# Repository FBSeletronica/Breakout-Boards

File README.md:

# Breakout-Boards
Arduino Breakouts boards for fun

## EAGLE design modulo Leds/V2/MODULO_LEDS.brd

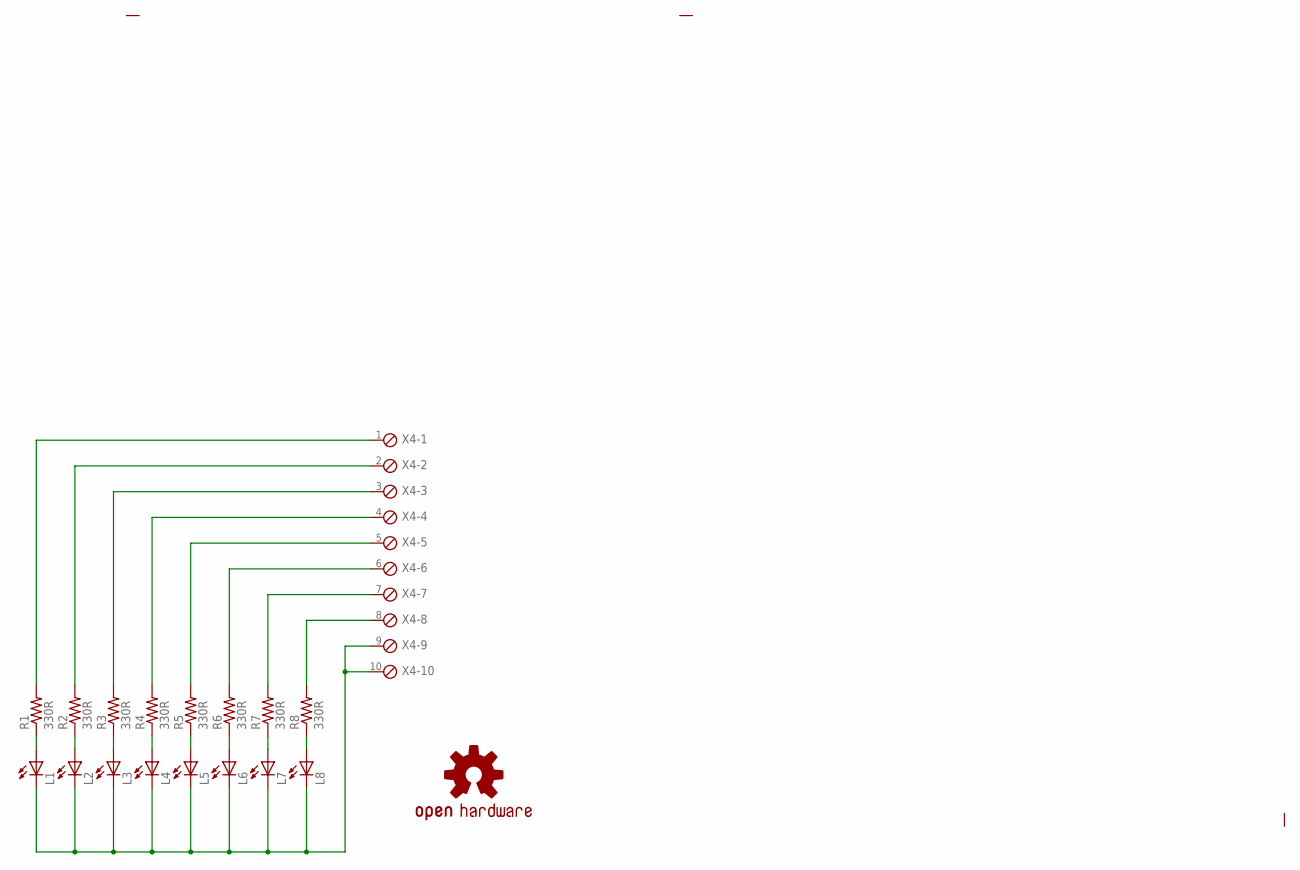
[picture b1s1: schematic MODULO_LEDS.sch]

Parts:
L1, L2, L3, L4, L5, L6, L7, L8: LED3MM
LOGO1: OSHW-LOGOM; OSHW-LOGO-M
R1, R2, R3, R4, R5, R6, R7, R8: 330R; AXIAL-0.4
X4: MPT10; 10POL254

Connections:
unnamed: L1.A, R1.P$1 (1)
unnamed: L2.A, R2.P$1 (1)
unnamed: L3.A, R3.P$1 (1)
unnamed: L4.A, R4.P$1 (1)
unnamed: L1.K (C), L2.K (C), L3.K (C), L4.K (C), L5.K (C), L6.K (C), L7.K (C), L8.K (C), X4.9, X4.10
unnamed: L5.A, R5.P$1 (1)
unnamed: L6.A, R6.P$1 (1)
unnamed: L7.A, R7.P$1 (1)
unnamed: L8.A, R8.P$1 (1)
unnamed: R1.P$2 (2), X4.1
unnamed: R2.P$2 (2), X4.2
unnamed: R3.P$2 (2), X4.3
unnamed: R4.P$2 (2), X4.4
unnamed: R5.P$2 (2), X4.5
unnamed: R6.P$2 (2), X4.6
unnamed: R7.P$2 (2), X4.7
unnamed: R8.P$2 (2), X4.8

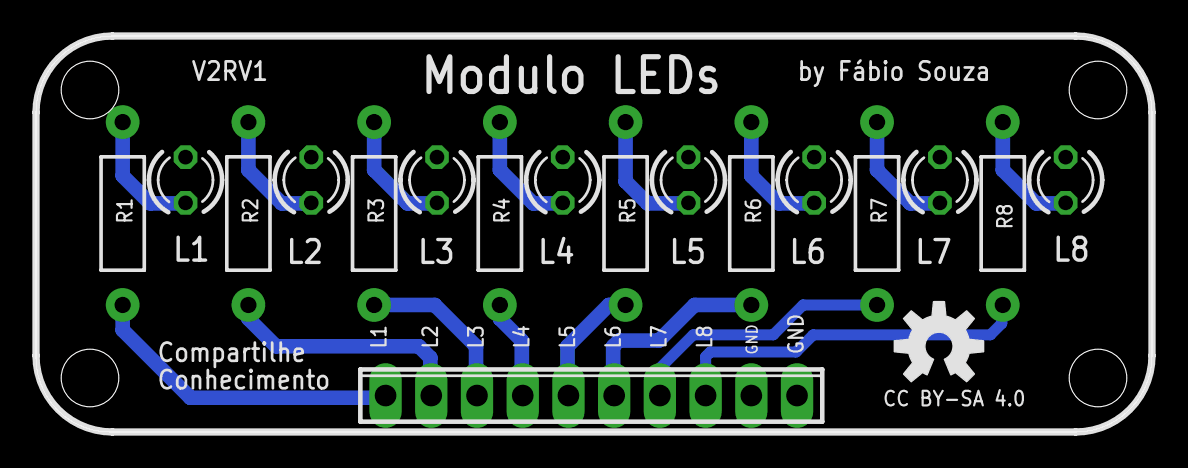
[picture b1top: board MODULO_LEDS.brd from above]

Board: 2 copper layers, 62.0 x 22.0 mm, 18 parts (0 on the bottom side), 17 nets.

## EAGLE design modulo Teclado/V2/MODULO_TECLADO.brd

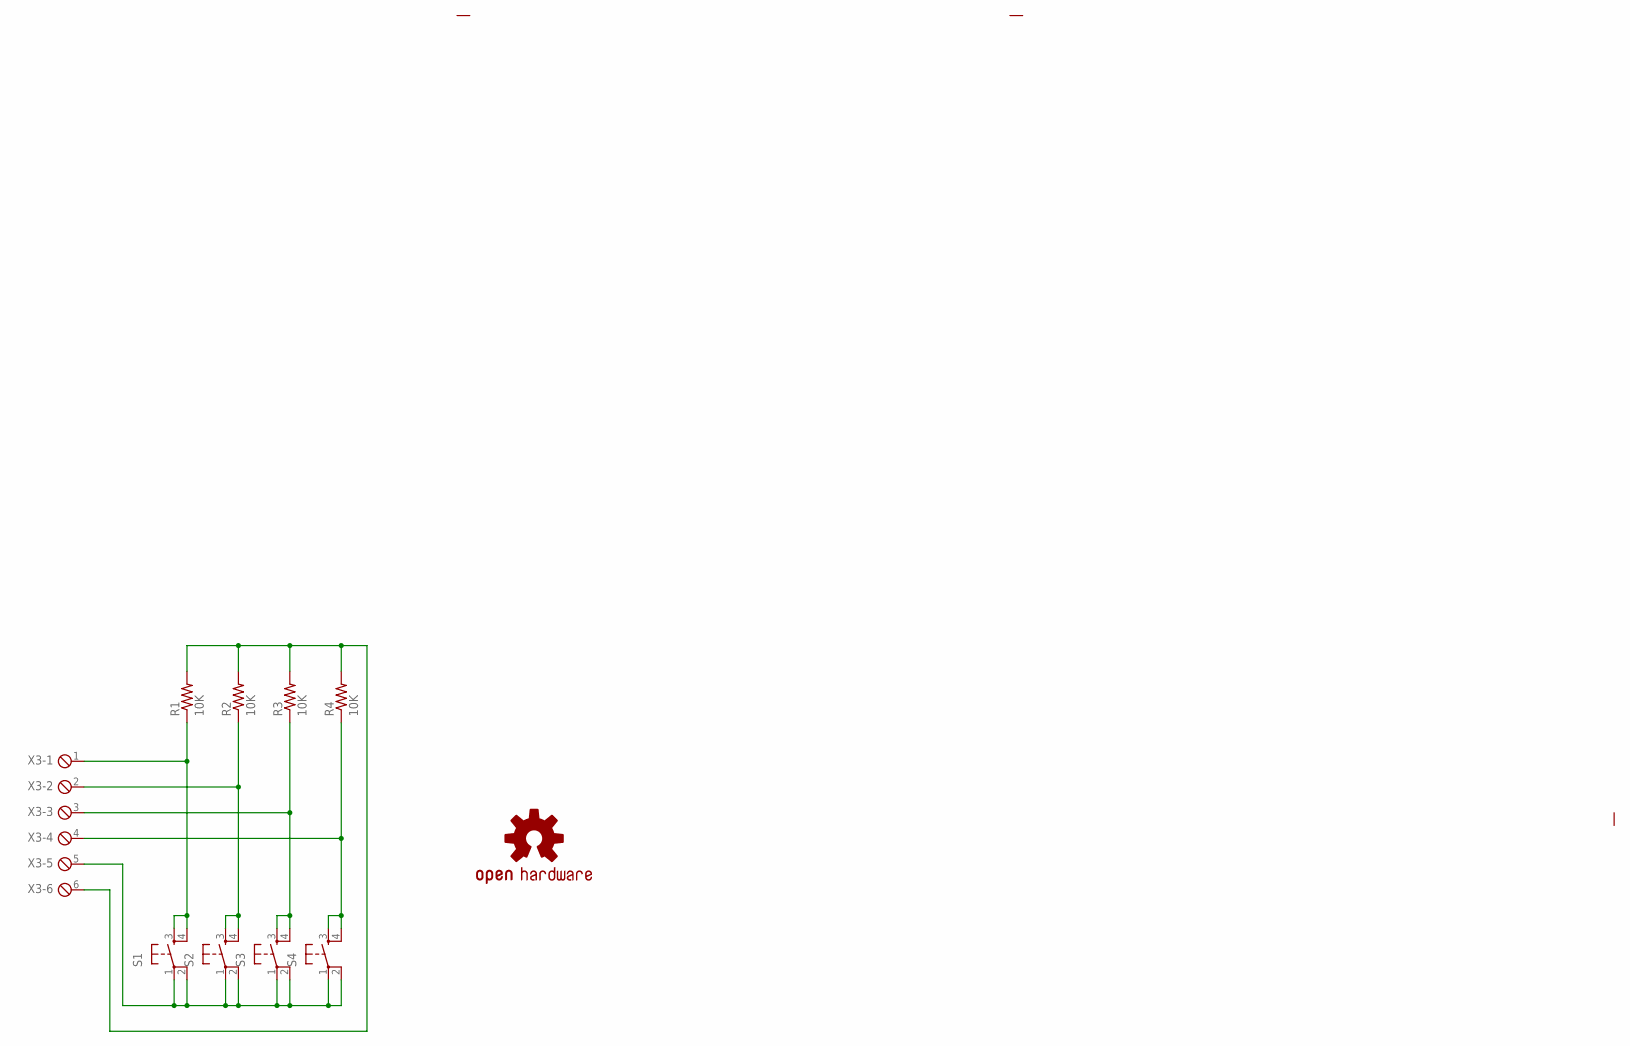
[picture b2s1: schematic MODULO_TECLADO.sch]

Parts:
LOGO1: OSHW-LOGOM; OSHW-LOGO-M
R1, R2, R3, R4: 10K; AXIAL-0.4
S1, S2, S3, S4: TAC_SWITCHPTH; TACTILE-PTH
X3: MPT6; 6POL254

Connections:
unnamed: R1.P$1 (1), S1.3, S1.4, X3.1
unnamed: R2.P$1 (1), S2.3, S2.4, X3.2
unnamed: R3.P$1 (1), S3.3, S3.4, X3.3
unnamed: R4.P$1 (1), S4.3, S4.4, X3.4
unnamed: S1.1, S1.2, S2.1, S2.2, S3.1, S3.2, S4.1, S4.2, X3.5
unnamed: R1.P$2 (2), R2.P$2 (2), R3.P$2 (2), R4.P$2 (2), X3.6

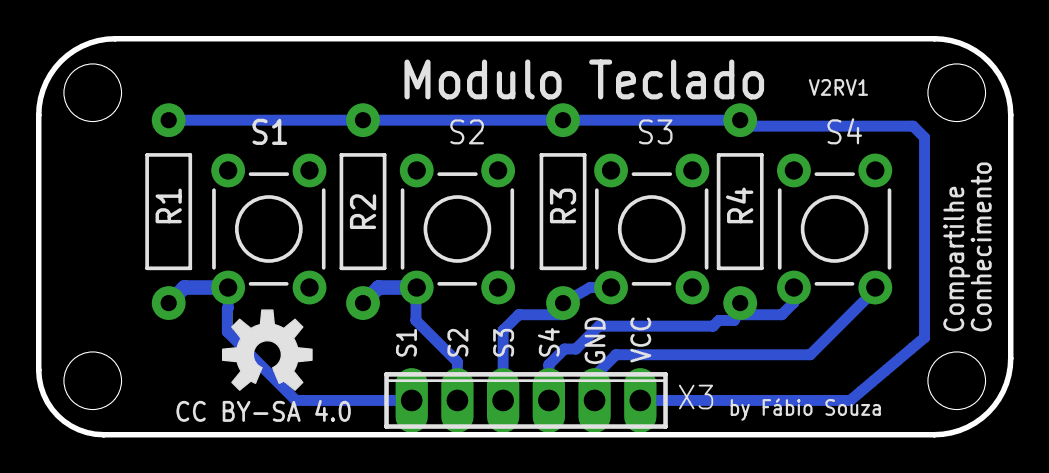
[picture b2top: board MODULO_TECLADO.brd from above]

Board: 2 copper layers, 54.0 x 22.0 mm, 10 parts (0 on the bottom side), 6 nets.

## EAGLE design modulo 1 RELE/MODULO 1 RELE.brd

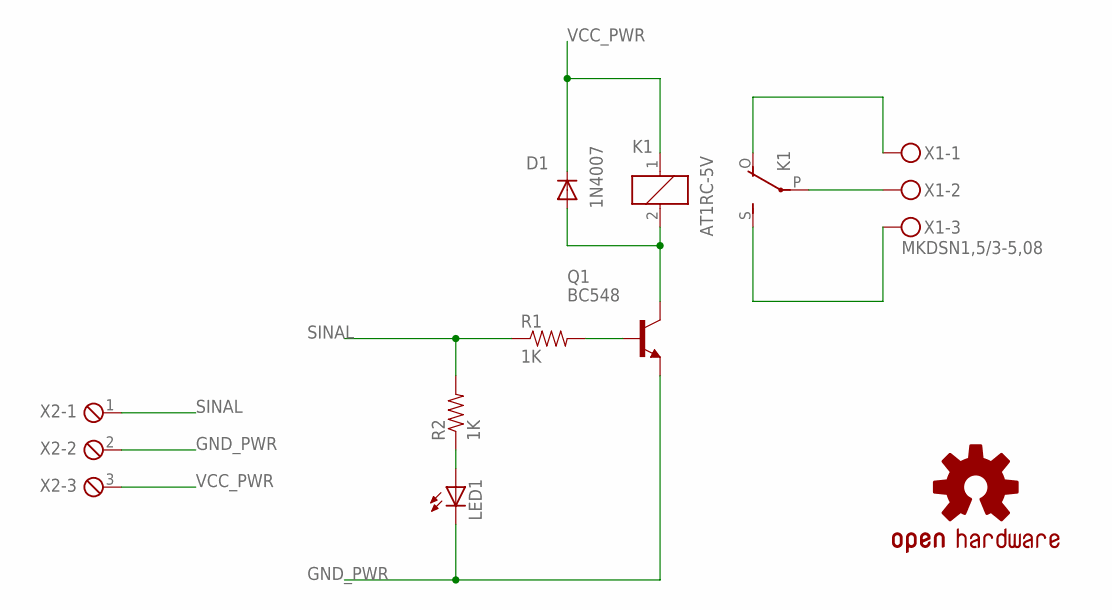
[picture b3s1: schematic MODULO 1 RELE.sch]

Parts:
D1: 1N4007; DIODE-1N4001
K1: AT1RC-5V; G5LE
LED1: LED3MM
LOGO1: OSHW-LOGOM; OSHW-LOGO-M
Q1: BC548; TO92-EBC
R1, R2: 1K; AXIAL-0.4
X1: MKDSN1,5/3-5,08
X2: MPT3; 3POL254

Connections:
GND_PWR: LED1.K (C), Q1.E, X2.2
unnamed: Q1.B, R1.P$2 (2)
unnamed: K1.O, X1.1
unnamed: LED1.A, R2.P$1 (1)
unnamed: K1.P, X1.2
unnamed: K1.S, X1.3
unnamed: D1.A, K1.2, Q1.C
SINAL: R1.P$1 (1), R2.P$2 (2), X2.1
VCC_PWR: D1.C, K1.1, X2.3

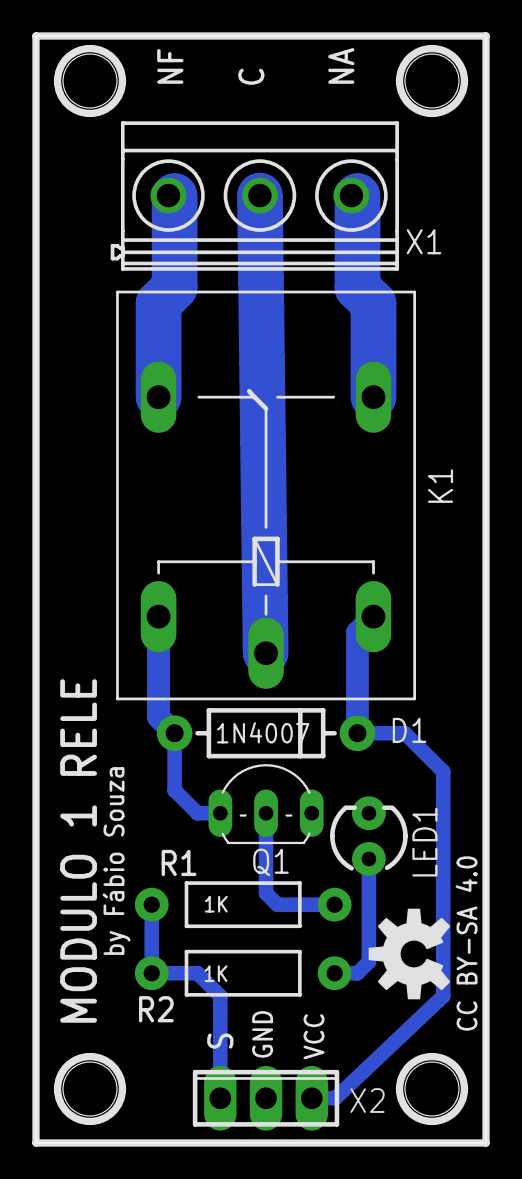
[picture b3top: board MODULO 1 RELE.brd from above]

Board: 2 copper layers, 25.0 x 61.5 mm, 9 parts (0 on the bottom side), 9 nets.

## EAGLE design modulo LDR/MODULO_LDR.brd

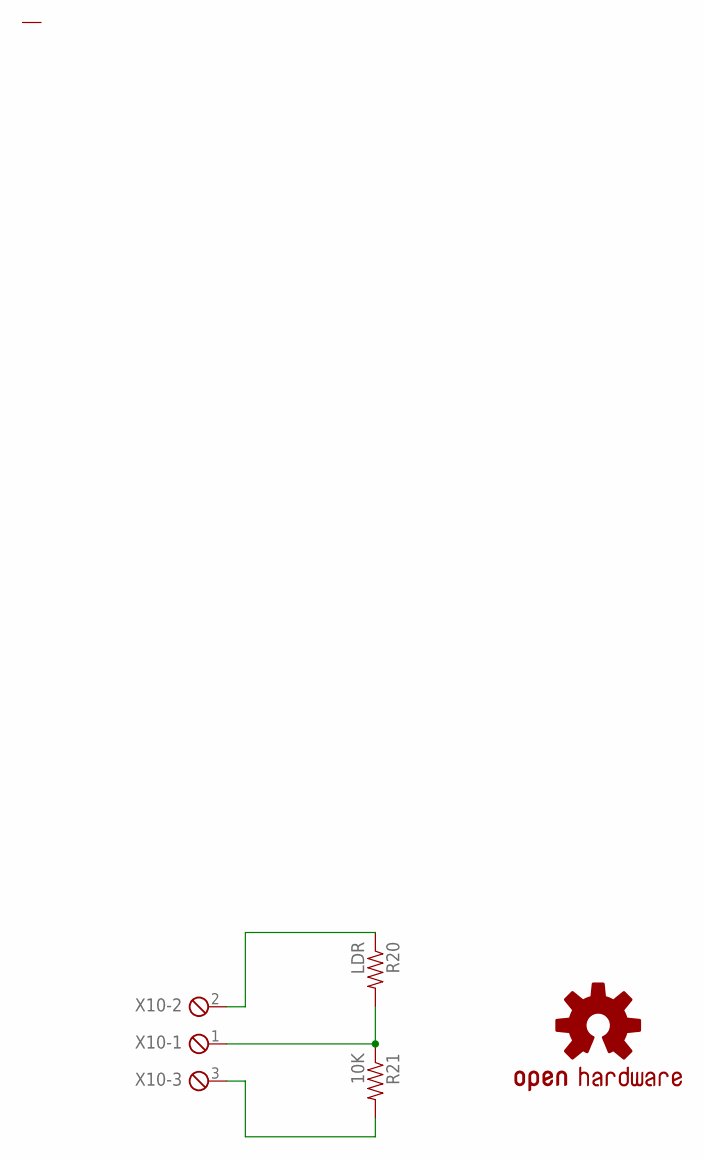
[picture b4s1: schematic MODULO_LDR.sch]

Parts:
LOGO1: OSHW-LOGOS; OSHW-LOGO-S
R20: LDR; 1/6W-RES
R21: 10K; AXIAL-0.4
X10: MPT3; 3POL254

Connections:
unnamed: R20.1, X10.2
unnamed: R21.P$2 (2), X10.3
unnamed: R20.2, R21.P$1 (1), X10.1

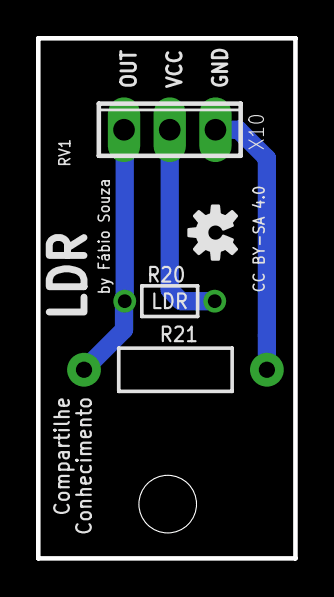
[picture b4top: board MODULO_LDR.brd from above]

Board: 2 copper layers, 14.3 x 28.9 mm, 4 parts (0 on the bottom side), 3 nets.

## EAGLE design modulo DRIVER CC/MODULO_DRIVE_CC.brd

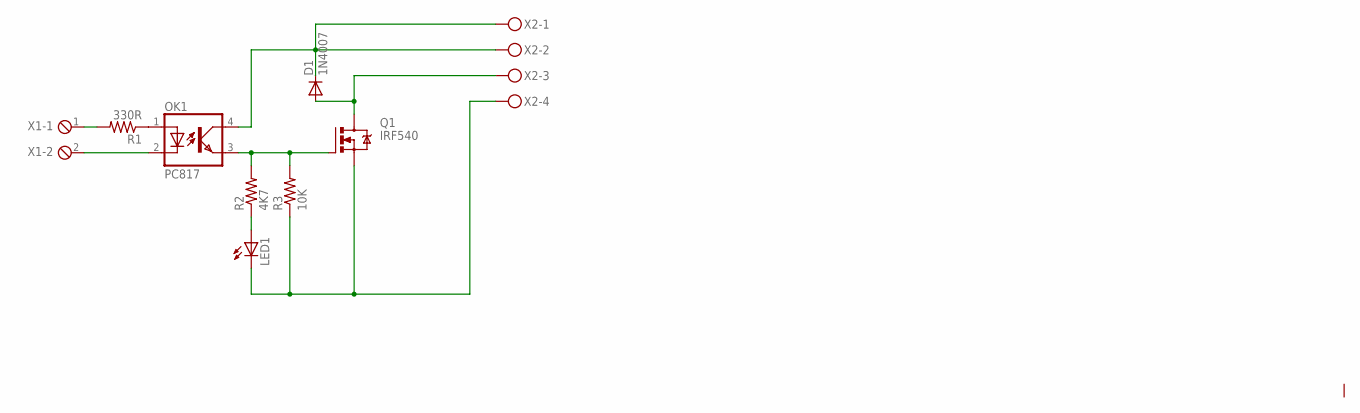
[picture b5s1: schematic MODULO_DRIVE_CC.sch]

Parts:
D1: 1N4007; DO41-10
LED1: LED3MM
OK1: PC817; DIL04
Q1: IRF540; TO220BV
R1: 330R; AXIAL-0.4
R2: 4K7; AXIAL-0.4
R3: 10K; AXIAL-0.4
X1: MPT2; 2POL254
X2: MKDSN1,5/4-5,08

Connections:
unnamed: D1.A, Q1.D, X2.3
unnamed: D1.C, OK1.4 (COL), X2.1, X2.2
unnamed: LED1.K (C), Q1.S, R3.P$1 (1), X2.4
unnamed: OK1.3 (EMIT), Q1.G, R2.P$2 (2), R3.P$2 (2)
unnamed: LED1.A, R2.P$1 (1)
unnamed: OK1.1 (A), R1.P$1 (1)
unnamed: R1.P$2 (2), X1.1
unnamed: OK1.2 (C), X1.2

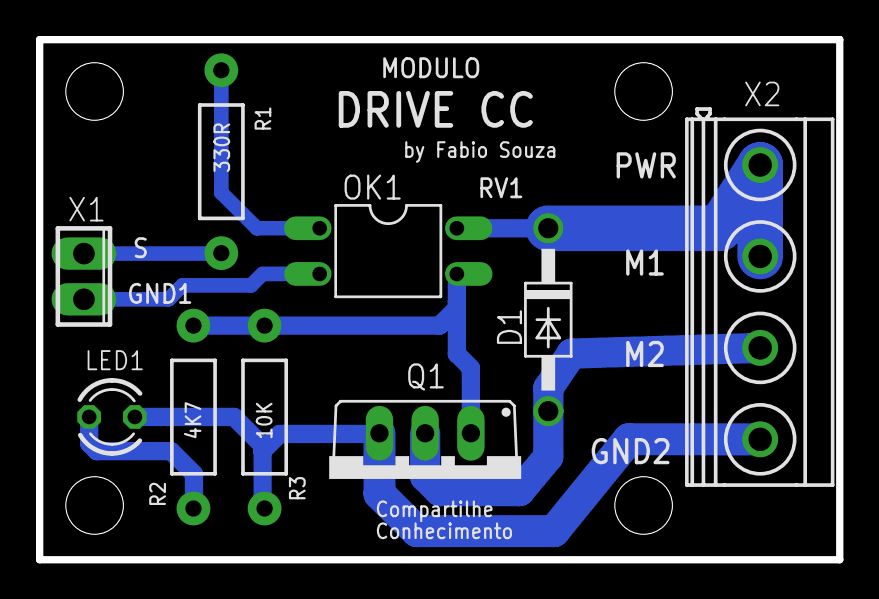
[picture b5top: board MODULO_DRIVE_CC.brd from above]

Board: 2 copper layers, 44.5 x 28.9 mm, 9 parts (0 on the bottom side), 8 nets.

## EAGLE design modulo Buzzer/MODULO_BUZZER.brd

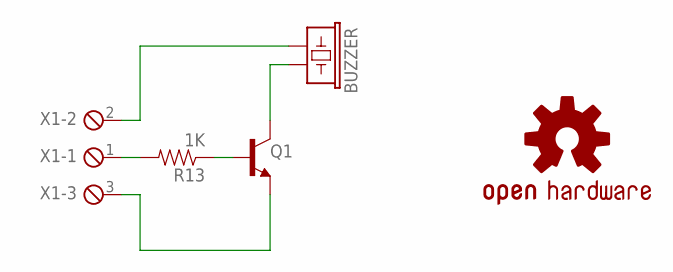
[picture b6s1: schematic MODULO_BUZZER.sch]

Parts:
BUZZER: BUZZERNS; BUZZER-12MM-NS
LOGO1: OSHW-LOGOM; OSHW-LOGO-M
Q1: BC548; TO92-EBC
R13: 1K; AXIAL-0.4
X1: MPT3; 3POL254

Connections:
unnamed: Q1.B, R13.P$1 (1)
unnamed: BUZZER.+ (1), X1.2
unnamed: BUZZER.- (2), Q1.C
unnamed: Q1.E, X1.3
unnamed: R13.P$2 (2), X1.1

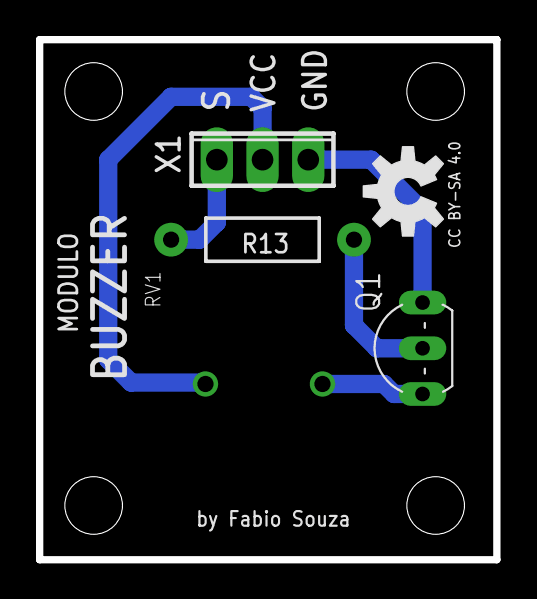
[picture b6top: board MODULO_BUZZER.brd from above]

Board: 2 copper layers, 25.4 x 28.9 mm, 5 parts (0 on the bottom side), 5 nets.

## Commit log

2017-06-30 :tada: Added .gitattributes & .gitignore files
2017-06-30 modulos
    some modules
2017-07-02 MÓDULO 1 RELE
2017-08-04 placas menores
    LEDS e Teclado
2017-08-04 imagens

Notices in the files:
modulo 1 RELE/MODULO 1 RELE.brd:
CC BY-SA 4.0
parts and their libraries:
SparkFun-Aesthetics: Licensing: Creative Commons ShareAlike 4.0 International - https://creativecommons.org/licenses/by-sa/4.0
